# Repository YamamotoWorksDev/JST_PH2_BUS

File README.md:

# JST PH2 BUS Module

This module splits power from a 2-pin PH connector into four outputs.  
It includes an ideal diode (LM66100) to provide reverse-polarity protection on the input connector and to block reverse current from the outputs back to the input.

## How to buy
- [Tindie(International)](https://www.tindie.com/products/yamamotoworks/ph2-bus-module/)
- [BASE(Japan)](https://miyworks.base.shop/items/138263232)

## Specification
- IO: 1 Input and 4 Outputs
- Input voltage range: 1.5–5.5(V)
- Maximum current: 1.5(A)
- Connector: JST PH2(S2B-PH-K-S(LF)(SN))
- Ideal Diode: [LM66100QDCKRQ1](https://www.ti.com/product/ja-jp/LM66100-Q1/part-details/LM66100QDCKRQ1)

## Application Example
- [JUMBLEQ](https://github.com/yamamo2shun1/JUMBLEQ)

## Size

## Photo

## License
The hardware design files in this repository are licensed under the
**CERN Open Hardware Licence Version 2 - Permissive (CERN-OHL-P-2.0)**.

Unless otherwise stated, the following are treated as hardware design files covered by CERN-OHL-P-2.0:

- KiCad schematic files
- PCB layout files

A copy of the license text is provided in the `LICENSE` file.

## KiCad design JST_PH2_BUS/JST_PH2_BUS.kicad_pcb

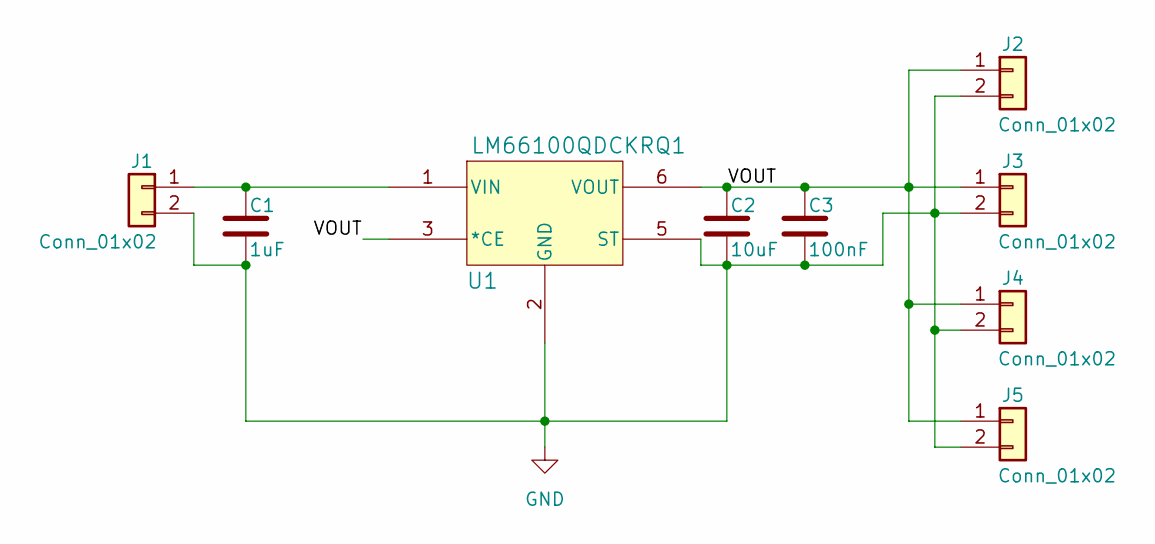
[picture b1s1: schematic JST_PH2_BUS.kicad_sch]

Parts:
C1: 1uF; C_0805_2012Metric
C2: 10uF; C_0805_2012Metric
C3: 100nF; C_0805_2012Metric
J1, J2, J3, J4, J5: Conn_01x02; JST_PH_S2B-PH-K_1x02_P2.00mm_Horizontal
U1: LM66100QDCKRQ1; SC70-6_DCK_TEX

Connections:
/VOUT: C2.1, C3.1, J2.1, J3.1, J4.1, J5.1, U1.3 (*CE), U1.6 (VOUT)
GND: C1.2, C2.2, C3.2, J1.2, J2.2, J3.2, J4.2, J5.2, U1.2 (GND), U1.5 (ST)
unnamed: C1.1, J1.1, U1.1 (VIN)

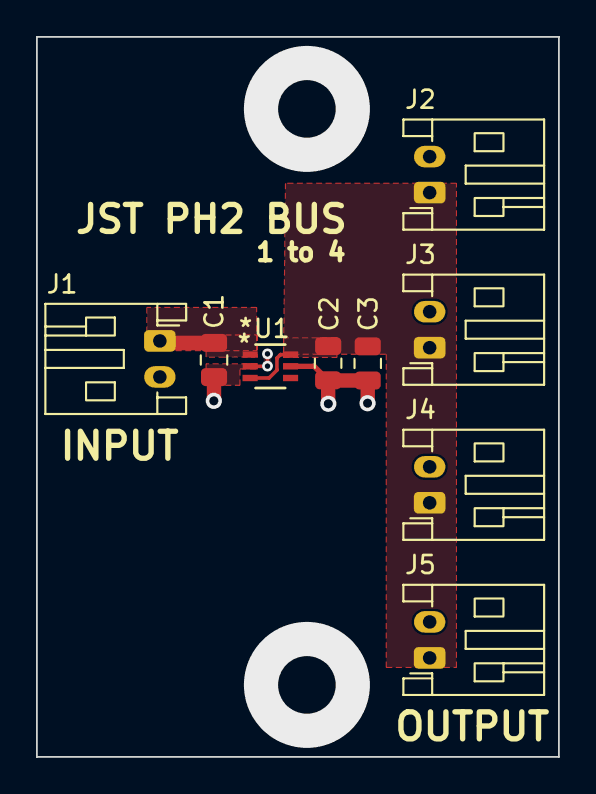
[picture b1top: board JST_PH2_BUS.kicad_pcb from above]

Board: 2 copper layers, 29.0 x 40.0 mm, 9 parts (0 on the bottom side), 3 nets.

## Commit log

2026-03-08 Add Kicad project files.
2026-03-08 Ignore jlcpcb and backup folders.
2026-03-08 Update README with specifications and size details
    Added specifications and size information to README.
2026-03-08 Add CERN Open Hardware License section to README
    Added license information for hardware design files.
2026-03-08 Add LICENSE.
2026-03-08 Provide Dimension information
2026-03-08 Rename LICENSE.md to LICENSE
    Update the reference in README.md to reflect the renamed license file.
2026-03-08 Renewed
2026-03-08 Move JST_PH2_BUS project files into a subdirectory
2026-03-08 Add schematic PDF for revision A
2026-03-08 Move schematic PDF to the root directory
2026-03-10 Enhance README with module description and specs
    Added a brief description of the module's functionality and clarified the input/output specification.
2026-03-10 Update README with buying info and photo section
    Added purchasing information and photo section to README.
2026-03-11 Add photos to README.md
2026-03-12 Change the 3D model data path settings.
2026-03-12 Update purchase link in README
2026-03-12 Update specifications in README.md
    Added input voltage range and maximum current specifications.
2026-03-13 Add Tindie link for purchasing options
2026-04-07 Add application example section to README
